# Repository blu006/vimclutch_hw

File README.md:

# vimclutch_hw
vimclutch hardware

## Description
This is a vim clutch implementation. This project uses the Arduino ProMicro, three tactile switches, and two LEDs.  The top two tactile switches are for switching modes.  The LEDs to show which layer the clutch is in.  The foot pedal is soldered onto the board.

## References
[Link to QMK keyboard](https://github.com/qmk/qmk_firmware/tree/master/keyboards/blu/vimclutch)

## BOM
The following is a bill of materials for this build.

Note that the selected vendors provide a suggestion of the component and the maker may choose to substitute with equivalent components.  Cheaper, less reputable vendors often provide parts that are more than acceptable for use in this non-critical project.

### 3D
The components below comprise the mechanical components of the vim clutch.
#### Prints
All 3d printable components are designed to be printable without supports.  The "flat bottom" may need to be aligned to print on your build plate in your favorite 3d printing slicer.
| Component | Material | Special Instructions |
| -- | -- | -- |
|`Top Housing.stl`|Clear-ish|Optionally print using the transparent parts printing techniques discussed [in this article](https://www.cnckitchen.com/blog/transparent-fdm-3d-prints-are-clearly-stronger)|
|`Bottom Housing.stl`|Your choice of color|N/A|
|`Button Left.stl`|Your choice of color|May exclude if you are using tactile switches that are long enough|
#### Vitamins
| Component | Comments | Selected Vendors |
| -- | -- | -- | 
|M3 x 12mm Socket Head Screw |It may be possible to use only two instead of four.|[McMaster Carr 91290A117](https://www.mcmaster.com/91290A117/) <br /> [Bolt Depot 13637](https://www.boltdepot.com/Product-Details.aspx?product=13637)|
|M3 Nut|"" |[McMaster Carr 98676A100](https://www.mcmaster.com/98676A100/)|
|Cable Tie 2.5mm|For holding the foot pedal cable onto the PCB| [Digikey 2162-AL-04-18-9-C-ND](https://www.digikey.com/en/products/detail/advanced-cable-ties-inc/AL-04-18-9-C/10380608)|
|Foot Pedal|Any SPDT or SPST foot pedal should work. |[Adafruit 423](https://www.adafruit.com/product/423) <br /> [Digi-Key 1528-1137-ND](https://www.digikey.com/en/products/detail/adafruit-industries-llc/423/5353597) |
|Ferrite Bead| May be optional. See [interference](README.md#interference)|[Digi-Key 1934-1375-ND](https://www.digikey.com/en/products/detail/fair-rite-products-corp/0431167281/8593997) <br /> [Digi-Key 240-2077-ND](https://www.digikey.com/en/products/detail/laird-signal-integrity-products/28A2029-0A2/242805) <br /> [Digi-Key 240-2076-ND](https://www.digikey.com/en/products/detail/laird-signal-integrity-products/28A2029-0A0/242804)|
|Micro USB Cable|Should have this already|Select a preferred vendor.  Local convenience stores or general stores will likely carry this part.|

### PCB
Since the PCB was originally designed to be made on a makerspace CNC with readily-available parts, the components necessary are generic and substitutable.  These components can also be seen on the PCB BOM included in the PCB directory.

The PCB is fabbable using any online PCB fab.  The designed thickness is **1.6mm** and your mechanical components will fit best at this board thickness.
| Component | Value | Quantity | Description | Selected Vendors |
| -- | -- | -- | -- | -- |
|D\*|RED|2|Wide Angle LED.  Note that this LED is height constrained.  It's possible to sand down a normal 5mm LED to fit in this position.|[Digi-Key 754-2141-ND](https://www.digikey.com/en/products/detail/kingbright/WP9294SECK-J3/7318908)|
|R\*|2.7k|2|LED Current Limiting Resistor|[Digi-Key CR0805-FX-2701ELFCT-ND](https://www.digikey.com/en/products/detail/bourns-inc/CR0805-FX-2701ELF/3784809)|
|SW1|H4.3mm|1|Reset switch.  4.3mm actuator length to keep it recessed into the housing.  A longer switch is also acceptable if it's what you have.  Tested successfully with 5mm.|[Digi-Key 2223-TS02-66-43-BK-260-SCR-D-ND](https://www.digikey.com/en/products/detail/cui-devices/TS02-66-43-BK-260-SCR-D/15634273)|
|SW(2,3)|H5mm or H10mm|2|Layer toggle switch.  Pair with the `Button Left.stl` if 5mm high switches are used.  Other lengths will likely work fine but have not been tested. |[Digi-Key TS02-66-100-BK-260-SCR-D](https://www.digikey.com/en/products/detail/cui-devices/TS02-66-100-BK-260-SCR-D/15634307)|
|U1|ProMicro|1|Arduino Pro Micro 5v/16Mhz.  Possible to purchase from other, less reputable sources.  Breakaway header pins may be needed if the promicro does not already come with them.|[Digi-Key 1568-1060-ND](https://www.digikey.com/en/products/detail/sparkfun-electronics/DEV-12640/5140825)|

## Assembly
1. Assemble the PCB and the foot pedal
2. Assemble the 3d printed enclosure
3. Plug in, program
4. Enjoy

### Interference
Board revision A and its relatives had problems with interference.

Board revision B does not because it uses direct pull-down keys.

## Tools
* KiCAD 6.0
* Fusion 360
* Soldering Iron
* Hex Wrench
* (Optional) CNC

## Next Steps
Consider the possibility of using a microcontroller with a USB-C port instead.

## Project Expectations
This project is provided as a form of weblogging (see: blogging).  The designs provided are not guaranteed for mercantability or quality beyond the occasional one-off production from enthusiasts.

### Tolerances
The tolerances from the SLA files and f360 should be sized for reasonably accurate FDM 3d printers and nothing more.  Do not expect them to be right for MSLA, injection molding, or subtractive manufacturing.

### Expected Support for the Project
Feel free to start a conversation in the Issues on GitHub or on any other social media sites.

The author may be willing to adjust some tolerances if the files are not editable enough for potential users.

## History
Rev B was released which changed all keys to be directly driven by the keyboard controller.

## Contributing
Please leave feedback in the Issues tab on the ease of assembly and similar items.  Minor updates on "I had to file this part in this way" could potentially improve the assembly for other people.

## Acknowledgements
The author's local makerspace provided the 3d printers and CNC to make this project possible.  Thank you [MAG Laboratory!](https://www.maglaboratory.org/)

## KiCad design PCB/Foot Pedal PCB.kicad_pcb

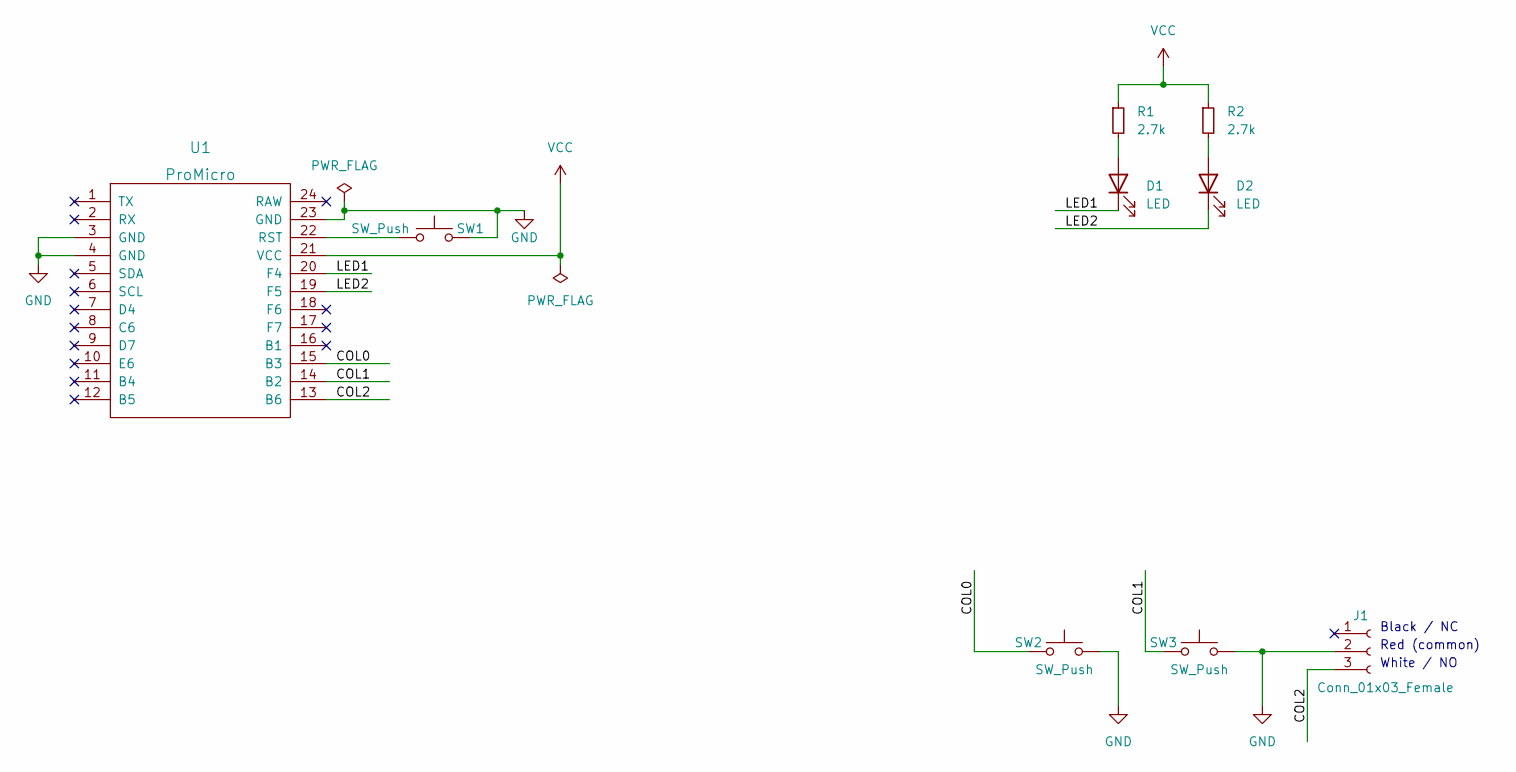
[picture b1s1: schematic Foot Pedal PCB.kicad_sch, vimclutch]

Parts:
D1, D2: LED; LED_D5.0mm
J1: Conn_01x03_Female; PinHeader_1x03_P2.00mm_Vertical
R1, R2: 2.7k; R_0805_2012Metric
SW1, SW2, SW3: SW_Push; SW_PUSH_6mm_H5mm
U1: ProMicro

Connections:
/COL0: SW2.1, U1.15 (B3)
/COL1: SW3.1, U1.14 (B2)
/COL2: J1.3, U1.13 (B6)
/LED1: D1.1 (K), U1.20 (F4)
/LED2: D2.1 (K), U1.19 (F5)
GND: J1.2, SW1.1, SW2.2, SW3.2, U1.3 (GND), U1.4 (GND), U1.23 (GND)
unnamed: D1.2 (A), R1.2
unnamed: D2.2 (A), R2.2
unnamed: SW1.2, U1.22 (RST)
VCC: R1.1, R2.1, U1.21 (VCC)

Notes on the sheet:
Black / NC
Red (common)
White / NO

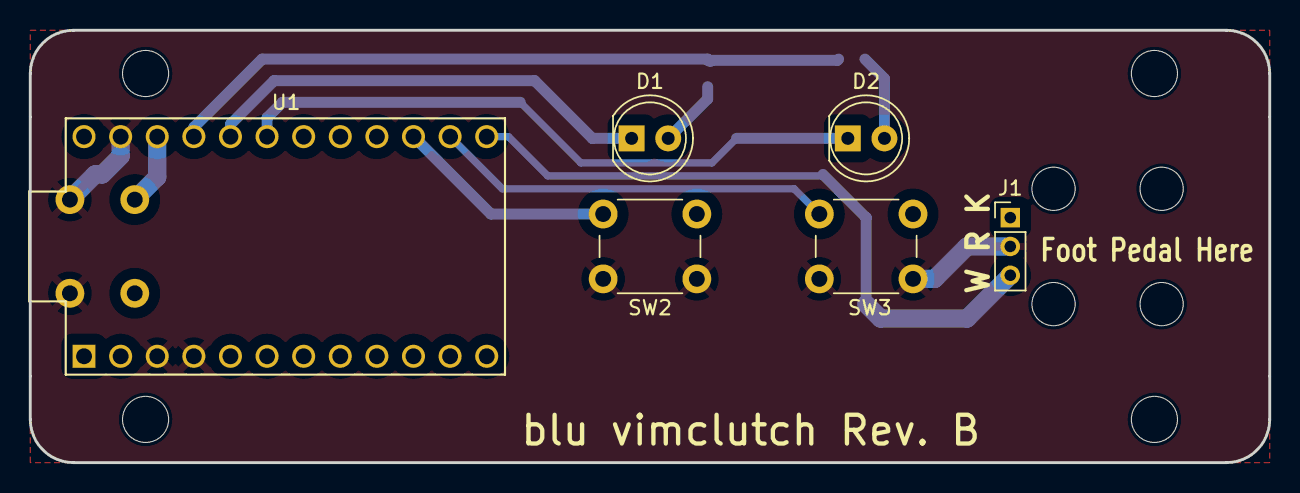
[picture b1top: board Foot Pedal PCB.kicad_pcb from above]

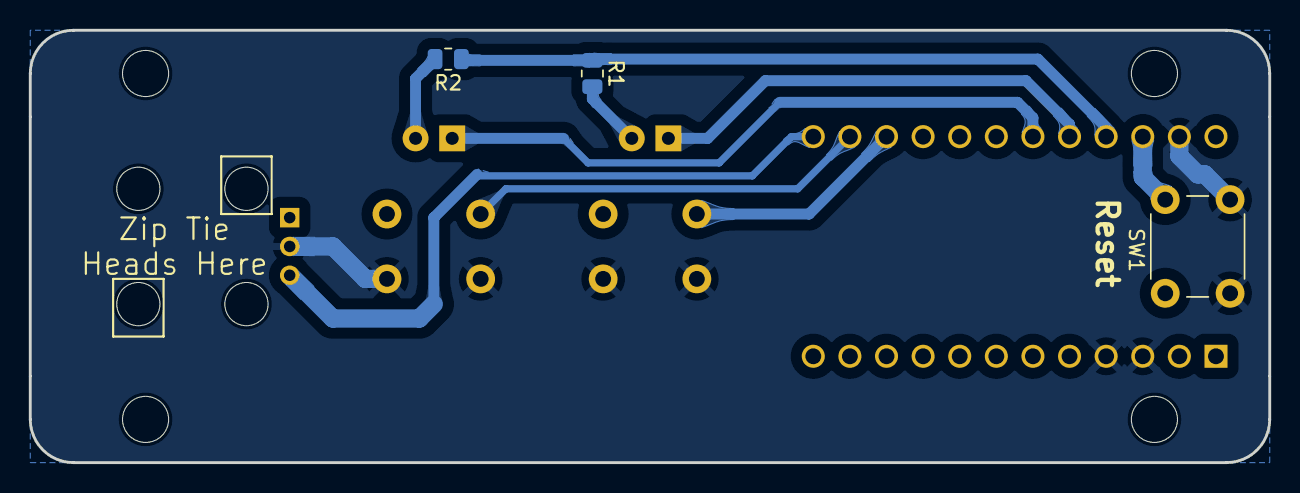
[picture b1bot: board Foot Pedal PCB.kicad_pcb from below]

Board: 2 copper layers, 86.0 x 30.0 mm, 9 parts (3 on the bottom side), 10 nets.

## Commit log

2023-03-07 Added the 3D files at least
2023-03-07 Added PCB
2023-03-07 PCB changes and incremental readme writes
2023-03-07 Readme changed... any suggestions for a local readme viewer?
2023-03-07 formatting
2023-03-07 added a newline in the readme
2023-03-07 Shortened link for better pagination
2023-03-07 Final commit of the night. Includes the BOM.
2023-03-07 Completed changes.
2023-03-08 Redid mounting holes for manufacturability. Edge cuts are a no-go for the zip tie holes.
2023-03-08 Zero (#1)
    The following commits are to be merged and committed to the main branch.
    * Added the 3D files at least
    * Added PCB
    * PCB changes and incremental readme writes
    * Readme changed... any suggestions for a local readme viewer?
    * formatting
2023-03-13 Added photos
    added text for the photos
2023-10-11 Added PDF and SVG plots of the schematic and PCB layers. Added revision B which has direct pull-down on all keys.
